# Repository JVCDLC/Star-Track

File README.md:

# ⭐ Star-Track by JVCDLC

## 🚀 Overview

**Star-Track** is an open-source project designed to transform a **manual telescope** into a fully **automated tracking system**.

It enables you to:
- 🔭 Automatically locate stars and planets  
- 🎯 Precisely orient the telescope  
- 🔄 Track celestial objects in real time  
- 🔍 Adjust focus dynamically  

The goal is simple: make astronomical observation **faster, easier, and more accessible**.

---

## 📚 Documentation

All setup instructions, technical details, and recommendations are available in the wiki:

👉 **[Star-Track Wiki](https://github.com/JVCDLC/Star-Track/wiki)**

---

## ⚙️ Features

### 🔧 Calibration
Ensure accurate positioning and alignment of your telescope.

https://github.com/user-attachments/assets/175ef95b-0138-4629-bef2-cc6909bee551

---

### 🌐 Web Interface
Control your telescope from a clean and intuitive interface.

---

### 🌌 Celestial Object Alignment
Automatically detect and select stars and planets.

https://github.com/user-attachments/assets/3bd77a46-6f4f-4f7e-8b46-55b38fbb0885

---

### 📡 Tracking
Keep your target centered with continuous real-time tracking.

https://github.com/user-attachments/assets/9ddb90b2-c935-49f4-bd0f-7d9df8abe6cd

---

---

## 📜 License

This project is licensed under the **GNU General Public License v2.0**.

You are free to:
- use
- modify
- distribute

as long as any derivative work is also distributed under the same license.

See the full license here: [LICENSE](./LICENSE)

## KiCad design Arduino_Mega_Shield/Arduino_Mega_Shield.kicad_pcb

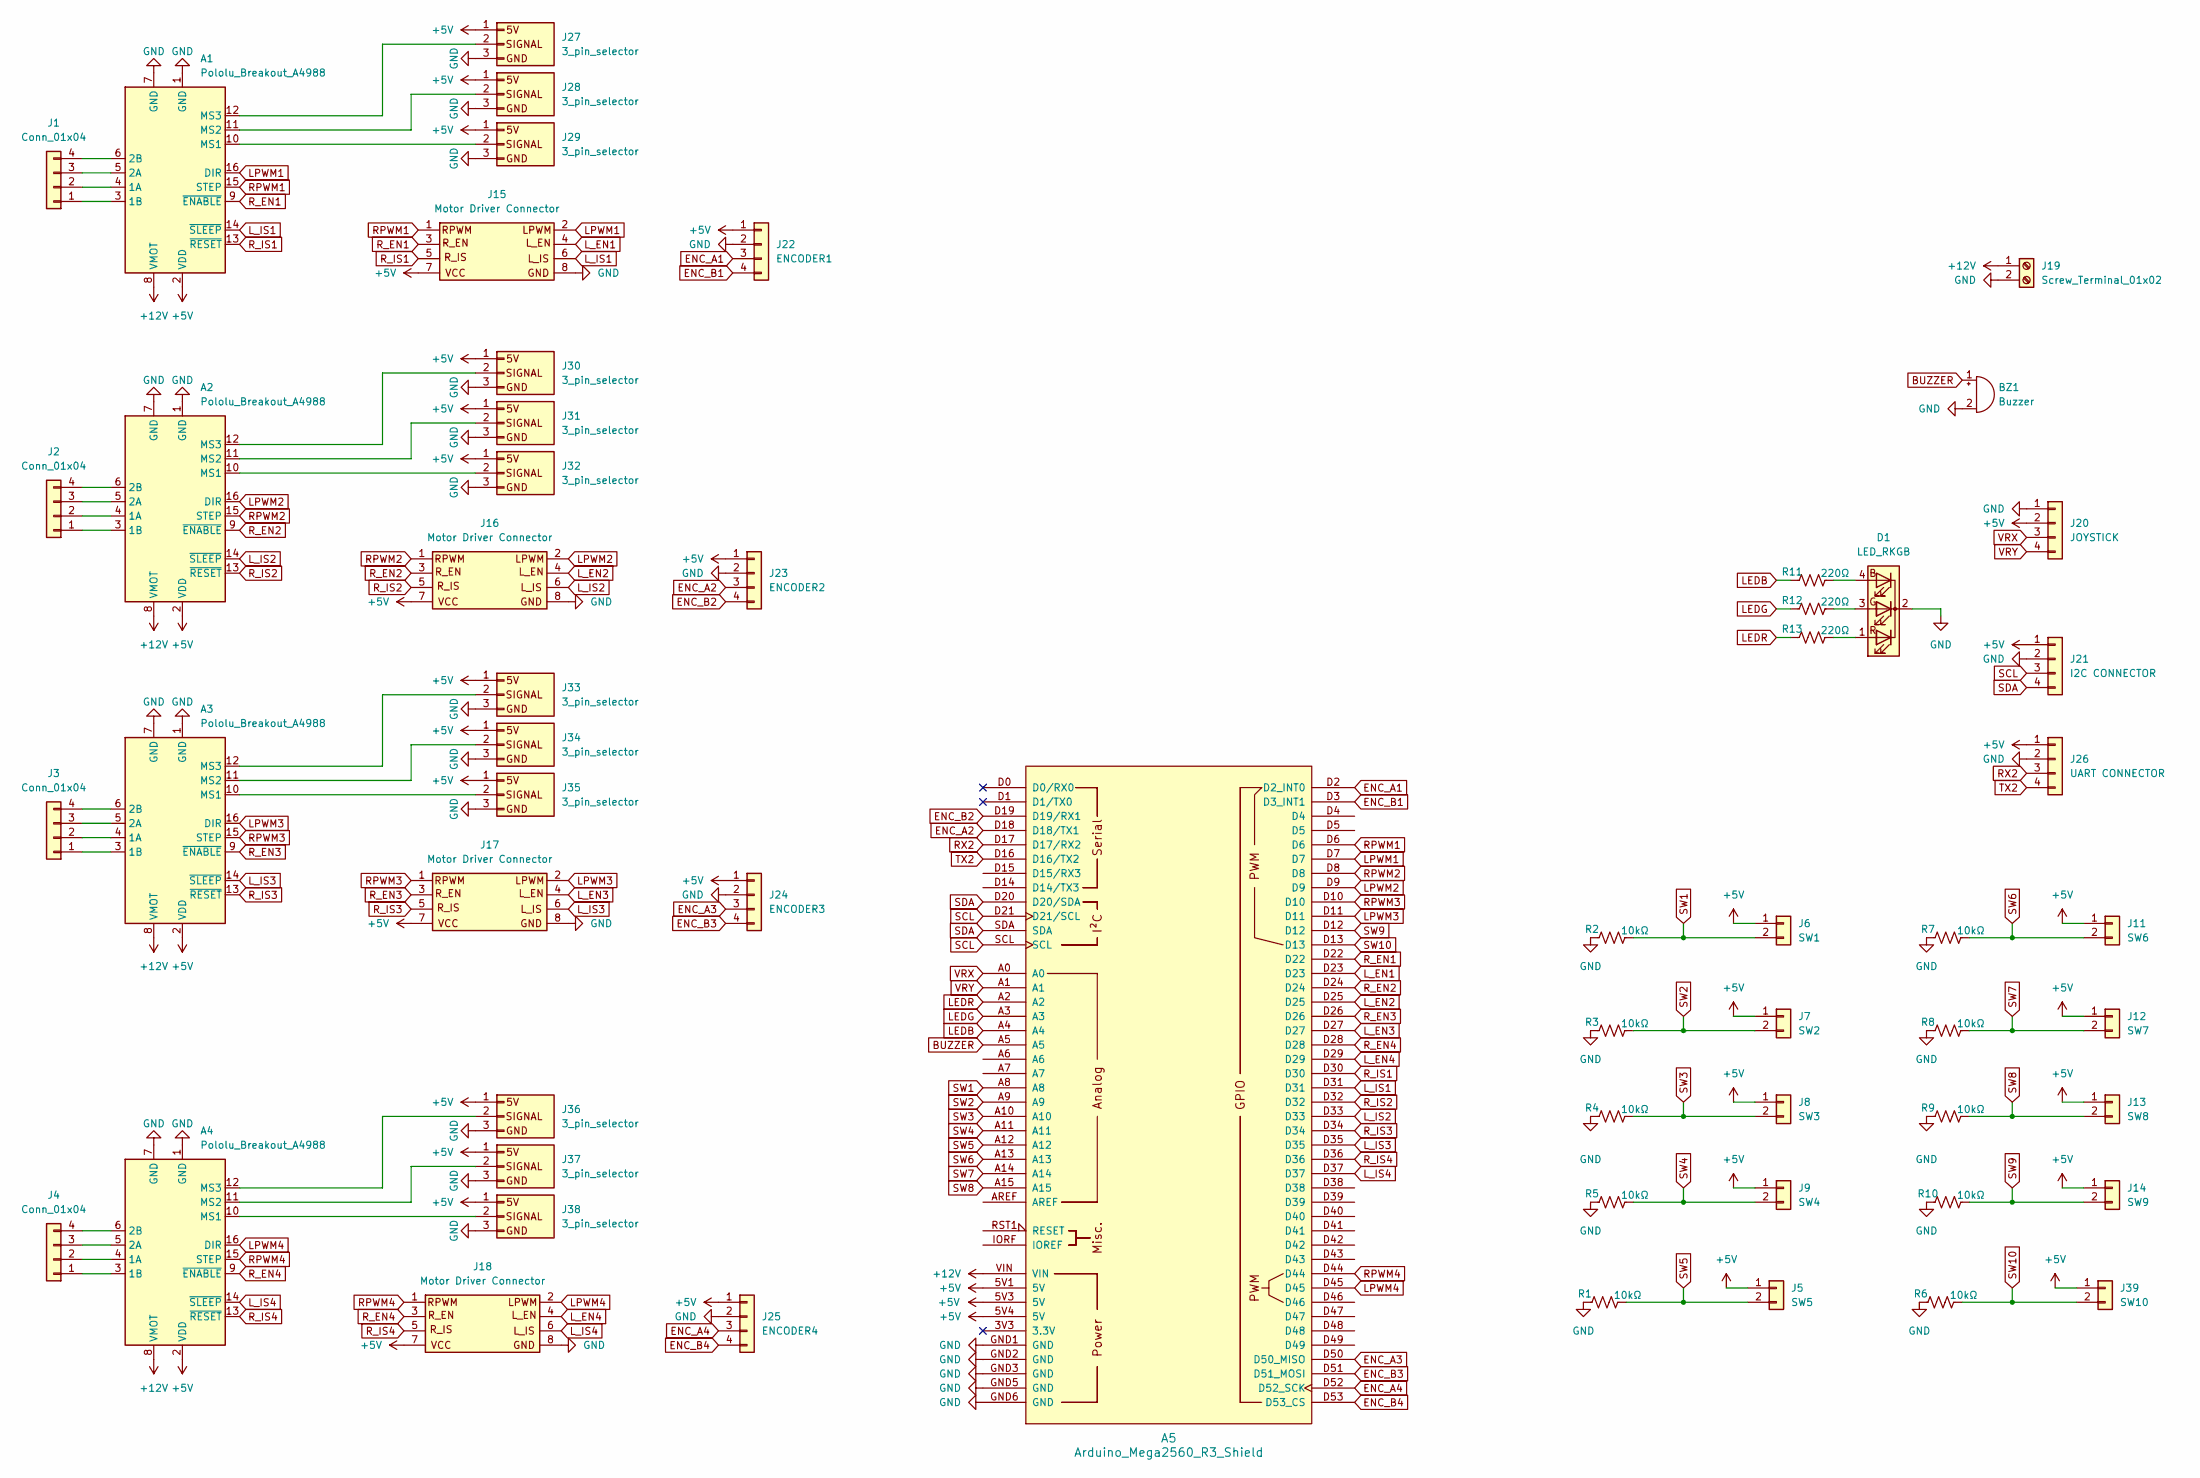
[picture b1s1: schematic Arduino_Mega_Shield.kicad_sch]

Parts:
A1, A2, A3, A4: Pololu_Breakout_A4988; Pololu_Breakout-16_15.2x20.3mm
A5: Arduino_Mega2560_R3_Shield
BZ1: Buzzer; Buzzer_12x9.5RM7.6
D1: LED_RKGB; LED_D5.0mm-4_RGB_Wide_Pins
J1, J2, J3, J4: Conn_01x04; JST_XH_B4B-XH-A_1x04_P2.50mm_Vertical
J5: SW5; PinHeader_1x02_P2.54mm_Vertical
J6: SW1; PinHeader_1x02_P2.54mm_Vertical
J7: SW2; PinHeader_1x02_P2.54mm_Vertical
J8: SW3; PinHeader_1x02_P2.54mm_Vertical
J9: SW4; PinHeader_1x02_P2.54mm_Vertical
J11: SW6; PinHeader_1x02_P2.54mm_Vertical
J12: SW7; PinHeader_1x02_P2.54mm_Vertical
J13: SW8; PinHeader_1x02_P2.54mm_Vertical
J14: SW9; PinHeader_1x02_P2.54mm_Vertical
J15, J16, J17, J18: Motor Driver Connector; PinHeader_2x04_P2.54mm_Vertical
J19: Screw_Terminal_01x02; TerminalBlock_RND_205-00232_1x02_P5.08mm_Horizontal
J20: JOYSTICK; JST_XH_B4B-XH-A_1x04_P2.50mm_Vertical
J21: I2C CONNECTOR; JST_XH_B4B-XH-A_1x04_P2.50mm_Vertical
J22: ENCODER1; JST_XH_B4B-XH-A_1x04_P2.50mm_Vertical
J23: ENCODER2; JST_XH_B4B-XH-A_1x04_P2.50mm_Vertical
J24: ENCODER3; JST_XH_B4B-XH-A_1x04_P2.50mm_Vertical
J25: ENCODER4; JST_XH_B4B-XH-A_1x04_P2.50mm_Vertical
J26: UART CONNECTOR; JST_XH_B4B-XH-A_1x04_P2.50mm_Vertical
J27, J28, J29, J30, J31, J32, J33, J34, J35, J36, J37, J38: 3_pin_selector; 3 pin selector
J39: SW10; PinHeader_1x02_P2.54mm_Vertical
R1, R2, R3, R4, R5, R6, R7, R8, R9, R10: 10kΩ; R_Axial_DIN0207_L6.3mm_D2.5mm_P7.62mm_Horizontal
R11, R12, R13: 220Ω; R_Axial_DIN0207_L6.3mm_D2.5mm_P7.62mm_Horizontal

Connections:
+5V: A1.2 (VDD), A2.2 (VDD), A3.2 (VDD), A4.2 (VDD), A5.5V1 (5V), A5.5V3 (5V), A5.5V4 (5V), J5.1, J6.1, J7.1, J8.1, J9.1, J11.1, J12.1, J13.1, J14.1, J15.7, J16.7, J17.7, J18.7, J20.2, J21.1, J22.1, J23.1, J24.1, J25.1, J26.1, J27.1, J28.1, J29.1, J30.1, J31.1, J32.1, J33.1, J34.1, J35.1, J36.1, J37.1, J38.1, J39.1
+12V: A1.8 (VMOT), A2.8 (VMOT), A3.8 (VMOT), A4.8 (VMOT), A5.VIN, J19.1
BUZZER: A5.A5, BZ1.1 (+)
ENC_A1: A5.D2 (D2_INT0), J22.3
ENC_A2: A5.D18 (D18/TX1), J23.3
ENC_A3: A5.D50 (D50_MISO), J24.3
ENC_A4: A5.D52 (D52_SCK), J25.3
ENC_B1: A5.D3 (D3_INT1), J22.4
ENC_B2: A5.D19 (D19/RX1), J23.4
ENC_B3: A5.D51 (D51_MOSI), J24.4
ENC_B4: A5.D53 (D53_CS), J25.4
GND: A1.1 (GND), A1.7 (GND), A2.1 (GND), A2.7 (GND), A3.1 (GND), A3.7 (GND), A4.1 (GND), A4.7 (GND), A5.GND1 (GND), A5.GND2 (GND), A5.GND3 (GND), A5.GND5 (GND), A5.GND6 (GND), BZ1.2 (-), D1.2 (K), J15.8, J16.8, J17.8, J18.8, J19.2, J20.1, J21.2, J22.2, J23.2, J24.2, J25.2, J26.2, J27.3, J28.3, J29.3, J30.3, J31.3, J32.3, J33.3, J34.3, J35.3, J36.3, J37.3, J38.3, R1.1, R2.1, R3.1, R4.1, R5.1, R6.1, R7.1, R8.1, R9.1, R10.1
LEDB: A5.A4, R11.1
LEDG: A5.A3, R12.1
LEDR: A5.A2, R13.1
LPWM1: A1.16 (DIR), A5.D7, J15.2
LPWM2: A2.16 (DIR), A5.D9, J16.2
LPWM3: A3.16 (DIR), A5.D11, J17.2
LPWM4: A4.16 (DIR), A5.D45, J18.2
L_EN1: A5.D23, J15.4
L_EN2: A5.D25, J16.4
L_EN3: A5.D27, J17.4
L_EN4: A5.D29, J18.4
L_IS1: A1.14 (~SLEEP), A5.D31, J15.6
L_IS2: A2.14 (~SLEEP), A5.D33, J16.6
L_IS3: A3.14 (~SLEEP), A5.D35, J17.6
L_IS4: A4.14 (~SLEEP), A5.D37, J18.6
unnamed: A1.4 (1A), J1.2
unnamed: A1.3 (1B), J1.1
unnamed: A1.5 (2A), J1.3
unnamed: A1.6 (2B), J1.4
unnamed: A1.10 (MS1), J29.2
unnamed: A1.11 (MS2), J28.2
unnamed: A1.12 (MS3), J27.2
unnamed: A2.4 (1A), J2.2
unnamed: A2.3 (1B), J2.1
unnamed: A2.5 (2A), J2.3
unnamed: A2.6 (2B), J2.4
unnamed: A2.10 (MS1), J32.2
unnamed: A2.11 (MS2), J31.2
unnamed: A2.12 (MS3), J30.2
unnamed: A3.4 (1A), J3.2
unnamed: A3.3 (1B), J3.1
unnamed: A3.5 (2A), J3.3
unnamed: A3.6 (2B), J3.4
unnamed: A3.10 (MS1), J35.2
unnamed: A3.11 (MS2), J34.2
unnamed: A3.12 (MS3), J33.2
unnamed: A4.4 (1A), J4.2
unnamed: A4.3 (1B), J4.1
unnamed: A4.5 (2A), J4.3
unnamed: A4.6 (2B), J4.4
unnamed: A4.10 (MS1), J38.2
unnamed: A4.11 (MS2), J37.2
unnamed: A4.12 (MS3), J36.2
unnamed: D1.4 (BA), R11.2
unnamed: D1.3 (GA), R12.2
unnamed: D1.1 (RA), R13.2
RPWM1: A1.15 (STEP), A5.D6, J15.1
RPWM2: A2.15 (STEP), A5.D8, J16.1
RPWM3: A3.15 (STEP), A5.D10, J17.1
RPWM4: A4.15 (STEP), A5.D44, J18.1
RX2: A5.D17 (D17/RX2), J26.3
R_EN1: A1.9 (~ENABLE), A5.D22, J15.3
R_EN2: A2.9 (~ENABLE), A5.D24, J16.3
R_EN3: A3.9 (~ENABLE), A5.D26, J17.3
R_EN4: A4.9 (~ENABLE), A5.D28, J18.3
R_IS1: A1.13 (~RESET), A5.D30, J15.5
R_IS2: A2.13 (~RESET), A5.D32, J16.5
R_IS3: A3.13 (~RESET), A5.D34, J17.5
R_IS4: A4.13 (~RESET), A5.D36, J18.5
SCL: A5.D21 (D21/SCL), A5.SCL, J21.3
SDA: A5.D20 (D20/SDA), A5.SDA, J21.4
SW1: A5.A8, J6.2, R2.2
SW2: A5.A9, J7.2, R3.2
SW3: A5.A10, J8.2, R4.2
SW4: A5.A11, J9.2, R5.2
SW5: A5.A12, J5.2, R1.2
SW6: A5.A13, J11.2, R7.2
SW7: A5.A14, J12.2, R8.2
SW8: A5.A15, J13.2, R9.2
SW9: A5.D12, J14.2, R10.2
SW10: A5.D13, J39.2, R6.2
TX2: A5.D16 (D16/TX2), J26.4
VRX: A5.A0, J20.3
VRY: A5.A1, J20.4

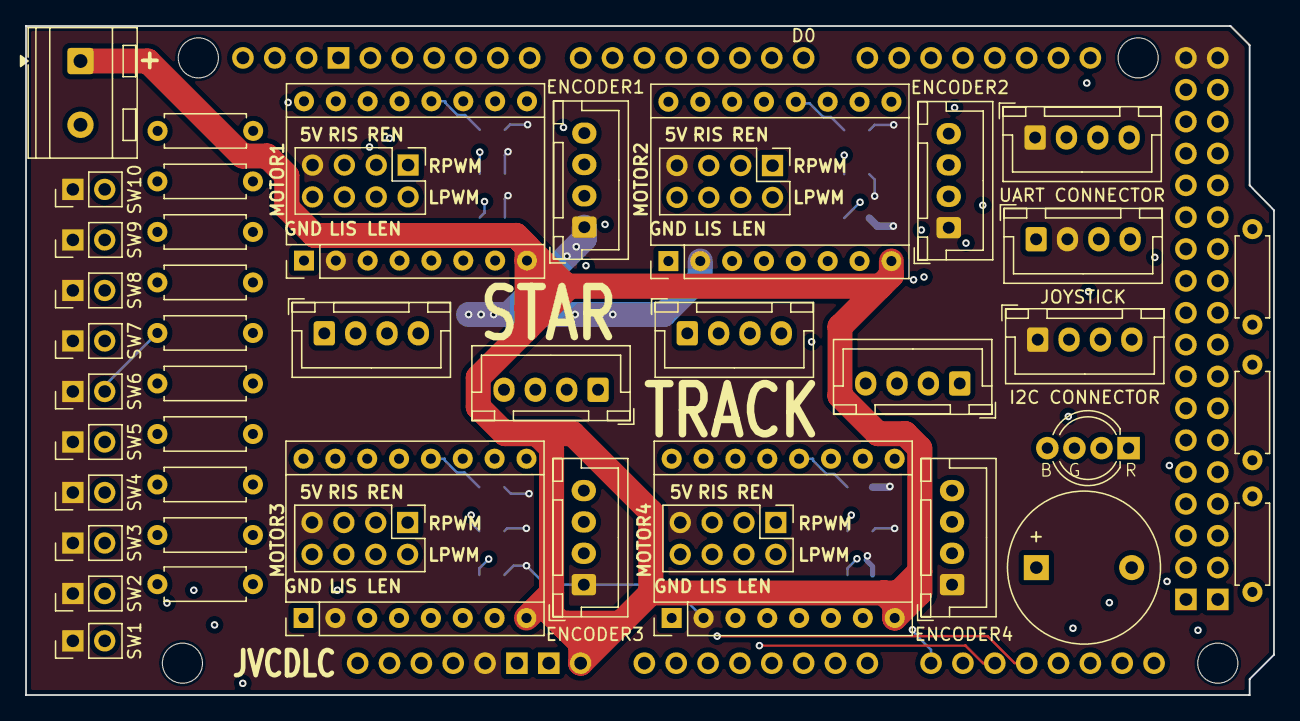
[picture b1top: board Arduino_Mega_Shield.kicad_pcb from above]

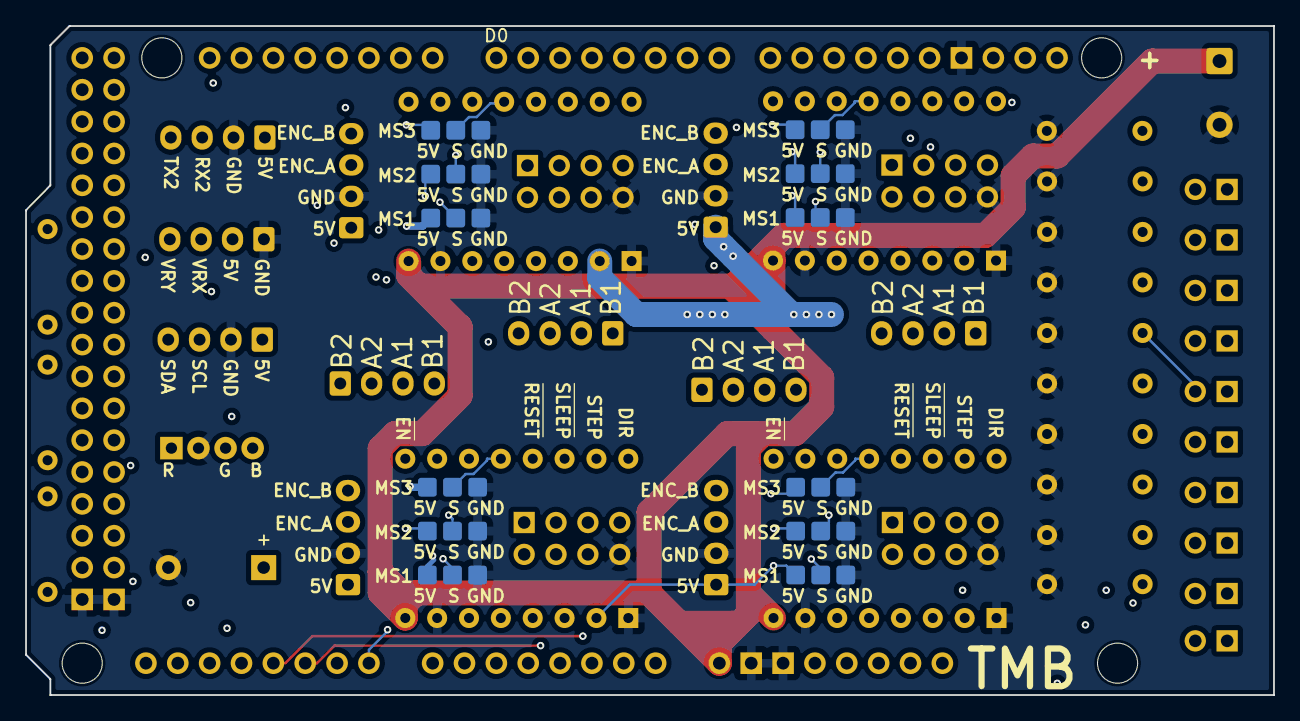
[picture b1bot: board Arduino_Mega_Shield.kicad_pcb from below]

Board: 4 copper layers, 99.5 x 53.3 mm, 58 parts (12 on the bottom side), 86 nets.

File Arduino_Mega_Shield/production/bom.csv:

Designator,Footprint,Quantity,Value,LCSC Part #
"A1, A2, A3, A4",Pololu_Breakout-16_15.2x20.3mm,4,Pololu_Breakout_A4988,
A5,Arduino_Mega2560_R3_Shield,1,Arduino_Mega2560_R3_Shield,
BZ1,Buzzer_12x9.5RM7.6,1,Buzzer,
D1,LED_D5.0mm-4_RGB_Wide_Pins,1,LED_RKGB,
"J1, J2, J3, J4",JST_XH_B4B-XH-A_1x04_P2.50mm_Vertical,4,Conn_01x04,
J11,PinHeader_1x02_P2.54mm_Vertical,1,SW6,
J12,PinHeader_1x02_P2.54mm_Vertical,1,SW7,
J13,PinHeader_1x02_P2.54mm_Vertical,1,SW8,
J14,PinHeader_1x02_P2.54mm_Vertical,1,SW9,
"J15, J16, J17, J18",PinHeader_2x04_P2.54mm_Vertical,4,Motor Driver Connector,
J19,TerminalBlock_RND_205-00232_1x02_P5.08mm_Horizontal,1,Screw_Terminal_01x02,
J20,JST_XH_B4B-XH-A_1x04_P2.50mm_Vertical,1,JOYSTICK,
J21,JST_XH_B4B-XH-A_1x04_P2.50mm_Vertical,1,I2C CONNECTOR,
J22,JST_XH_B4B-XH-A_1x04_P2.50mm_Vertical,1,ENCODER1,
J23,JST_XH_B4B-XH-A_1x04_P2.50mm_Vertical,1,ENCODER2,
J24,JST_XH_B4B-XH-A_1x04_P2.50mm_Vertical,1,ENCODER3,
J25,JST_XH_B4B-XH-A_1x04_P2.50mm_Vertical,1,ENCODER4,
J26,JST_XH_B4B-XH-A_1x04_P2.50mm_Vertical,1,UART CONNECTOR,
"J27, J28, J29, J30, J31, J32, J33, J34, J35, J36, J37, J38",3 pin selector,12,3_pin_selector,
J39,PinHeader_1x02_P2.54mm_Vertical,1,SW10,
J5,PinHeader_1x02_P2.54mm_Vertical,1,SW5,
J6,PinHeader_1x02_P2.54mm_Vertical,1,SW1,
J7,PinHeader_1x02_P2.54mm_Vertical,1,SW2,
J8,PinHeader_1x02_P2.54mm_Vertical,1,SW3,
J9,PinHeader_1x02_P2.54mm_Vertical,1,SW4,
"R1, R10, R2, R3, R4, R5, R6, R7, R8, R9",R_Axial_DIN0207_L6.3mm_D2.5mm_P7.62mm_Horizontal,10,10kΩ,
"R11, R12, R13",R_Axial_DIN0207_L6.3mm_D2.5mm_P7.62mm_Horizontal,3,220Ω,

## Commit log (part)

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2026-01-14 Update README.md
    Added OnShape Link
2026-01-14 Create field_of_view.py and update .gitignore. The python script evaluates the angular size of celestial bodies and compares it with the effective field of view of a telescope. The results are used t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
    Uncomment .idea/ and .vscode/ to make Git ignore those folders.
2026-01-14 Add requirements.txt List Python dependencies required to run the project. To install them, run: "pip install -r requirements.txt".
2026-01-16 Switch from static image to real-time webcam processing
    Replaces static image analysis with real-time video capture from the webcam. Adds live contour detection, center and diameter calculation, and overlays results on the video stream. Exits loop on 'q' 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
2026-01-16 Add References.txt with sky view resource
    Added a References.txt file containing a link to Stellarium Web for sky view by date.
2026-01-27 Add initial ESP-32 embedded and Python communication code
    Added PlatformIO project structure for ESP-32, including .gitignore, configuration, and a basic Arduino sketch that echoes serial messages with an ACK prefix. Also added a Python script to send and r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
2026-01-27 Add motor control request function for ESP-32
    Introduced Motor enum and send_request_motor function to send motor position requests to ESP-32 and handle acknowledgments. Updated main loop to demonstrate motor control requests and improved serial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
2026-01-28 Add motor control and encoder handling for ESP32
    Replaced Mega2560 config with ESP32 in platformio.ini. Implemented encoder reading, BTS7960 motor driver control, and basic PID logic in main.cpp. Enhanced serial command parsing and response. Update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
2026-01-28 Refactor motor control and add constants header
    Moved motor and encoder constants to a new motor_constants.hpp file for better organization and maintainability. Updated main.cpp to use the new constants, refactored variable names for clarity, and 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
2026-01-30 Update motor pin mappings and Python control loop
    Added color-coded comments to motor pin definitions and updated pin assignments for RA motor in motor_constants.hpp. Modified main.py to incrementally update the target angle for the RIGHT_ASCENSION 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
2026-01-30 Typing error correction in field_of_view.py script.
2026-02-03 Add ESP32-C3 MPU6050 accelerometer project
    Add a new PlatformIO project for ESP32-C3 to read an MPU6050 accelerometer. New files: .gitignore, platformio.ini (esp32-c3-devkitm-1, Arduino framework, USB build flags, Adafruit MPU6050/Unified Sen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
2026-02-03 Add RA motor support and PID + calibration
    Extend motor control to support a second (RA) motor and improve PID control and calibration. Key changes:
    - Add RA-specific encoder state, ISR, drive, reading, PID state and update functions.
    - Split DEC drive/encoder functions and refactor update_motor into DEC_update_motor and RA_update_motor; combined update_motor calls both.
    - Add integral (Ki) term with anti-windup for both motors and reset integral on new targets.
    - Replace single minimal-PWM detection with calibrate_minimum_PWM() that tests DEC and RA separately and stores DEC_pwm_min_real and RA_pwm_min_real.
    - Update setup() to initialize RA hardware, attach RA interrupts, and configure PWM
2026-02-03 DEC motor functionning, RA motor not working
    Adjust motor control parameters and improve calibration/debugging:
    - Set initial minimal PWM for both motors to 150.
    - Enable REN/LEN lines in DEC/RA drive functions before writing PWM.
    - Change RA driver PWM pin (RA_RPWM) from 15 to 17.
    - Increase RA PID proportional gain (RA_Kp) from 15.0 to 100.0.
    - Improve minimum-PWM detection: add serial logging, increase sample delay, raise motion threshold, and alter RA search start value.
2026-02-11 Working version!! Keyboard control; refine calibration & pins
    Add interactive keyboard control to Python client and harden motor calibration in firmware.
    Python: import msvcrt and add a non-blocking keyboard loop to send WASD controls and adjust speed with arrow keys (send_request_motor helper added). The previous continuous test loop is commented out.
    Firmware (ESP32): change DEC_LPWM and RA_LPWM pin assignments, add DEC_pwm_start_max and RA_pwm_start_max, and set RA gearbox to 900. Improve minimum PWM detection by printing motor-specific test mes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
2026-02-11 Use discrete speed presets with index
    Replace continuous speed_factor stepping with a discrete list of calibrated speed_values and a speed_index. Initialize speed_factor from speed_values[speed_index] and remove speed_step/min/max. Up/do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
2026-02-15 Update KiCad PCB (Pololu A4988) and ESP32 code
    Replace Arduino Mega shield footprint with a Pololu A4988 breakout footprint and reorganize PCB item positions/annotations (silkscreen, fab, footprint properties, net index adjustments). Add several 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
2026-02-16 Update code to analyse image and rename pictures
2026-02-17 Revise KiCad PCB footprints and add backups
    Large update to the Arduino_Mega_Shield KiCad project: modified .kicad_pcb/.kicad_prl/.kicad_pro/.kicad_sch to replace and update connector footprints (JST XH, pin headers), adjust pad shapes/drills,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
2026-02-18 Avancement on the electric shemas and some fixe on the PCB
2026-02-18 Some mast modification before changing for a Arduino Mega
2026-02-18 rencenter movemanual
2026-02-18 Change the code to work on a Arduino Mega and change the timers to be silent
    Switch project from ESP32 to ATmega2560 (PlatformIO env changed to megaatmega2560). Replace ESP32 ledc PWM APIs with Arduino analogWrite/pinMode and configure timer prescalers (TCCRnB) for quieter PW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
2026-02-23 PCB trace, but not verified
2026-02-24 First revision of the PCB
2026-02-24 Refactor movement control and update vision
    Recenter.py: Large refactor of movement/control logic — renamed and uppercased constants, added Skyfield timescale, introduced MOVEMENTSTATE enum, implemented raTracking, rotateXYtoAltAz, moveManuall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
    astrononic_function.py: Minor cleanup around main() and visible-catalog printing (whitespace/comment adjustments).
    recording_asi.py: Adjusted ASI camera defaults (gain/exposure), switched to RAW16 for deep-sky capture and fixed frame dtype/reshape to
2026-02-24 Add Jupiter video processing script
    Adds Software/Vision/src/video_test.py: a simple OpenCV pipeline that downsamples frames, thresholds and finds largest contour to locate a center, computes focus via Laplacian variance (with a rollin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
2026-03-01 Final version of the PCB
2026-03-07 Refactor of the Arduino code to improve readability and debugging
2026-03-09 Add astronomical operator and recentering functionality; remove unused recenter.py
2026-03-10 Enhance FOCUS motor control and tuning
    Adjust FOCUS control parameters and add safety/behavior changes.
    - constants.hpp: set FOCUS_gearbox to 75.0 and increase FOCUS_Kp to 1.0 to correct gearing and strengthen proportional control.
    - motors.cpp:
    - In FOCUS_drive_motor invert/constrain PWM to match wiring and prevent movement into switch by zeroing PWM when switch1 is triggered.
    - Increase delay in FOCUS_find_minimum_PWM() calibration from 200ms to 400ms.
    - Call FOCUS_update_motor() from update_motor() so focus is updated together with other axes.
2026-03-11 UpdateCatalog w rising and setting
2026-03-11 Update catalog rising and setting
2026-03-11 Add phone communication features with WebSocket and video streaming basically adding the whole UI - Implemented app.js for handling video stream and WebSocket communication. - Added main.py to contro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
2026-03-11 NOT WORKING Detect RA angle range; reduce start PWM
    Lowered PWM start maxima (DEC/RA/FOCUS) from 150 to 120 to reduce calibration drive power. Implemented RA angle-range detection: added RA_find_angle_range(), global min/max angle variables, and proto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
2026-03-14 - Developed a complete multi-pass autofocus state machine (sweep, analyze, lock, and track) with previous code from JP. - Implemented a highly realistic `ArduinoController` simulator featuring dual-P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
2026-03-20 Try to debug the code
    Add an exported interactive BOM (ibom.html) for the Arduino_Mega_Shield, including the embedded CSS/JS viewer (Split.js, LZString, pointer-event polyfills, etc.). Also apply updates to the ESP-32 emb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
2026-03-21 Calibration of declimation is working with switch
2026-03-22 The RA calibration is almost working
    Refine motor calibration routines for RA/DEC and add focus calibration. Changes include: calling RA_find_angle_range() from setup; removing unused static vars; tightening encoder centering threshold 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
2026-03-25 Finally have a working version of the calibration.
2026-03-27 Refactor motor control and serial protocol for improved clarity and functionality
    - Enhanced MotorState and MotionMode enums with detailed comments for better understanding of each state.
    - Updated PidConfig, MotorRuntimeConfig, LimitConfig, CalibrationConfig, and PrecisionConfig structures with descriptive comments for clarity on their purpose and usage.
    - Improved MotorBase class documentation, outlining its responsibilities and design principles.
    - Refined MountController class with comprehensive comments explaining its architecture, usage, and member functions.
    - Added detailed comments in SerialProtocol class to clarify the parsing logic and command structure.
    - Introduced a new DEBUG_F
2026-03-27 degree to ticks in astronomic operator
2026-03-28 improve readability of electrical shematic
2026-03-28 Revise draw.io schematic: layout & components
    Update Electric shematic.drawio: reorganize component geometry and edges, reposition Raspberry Pi and Camera, rename/expand the Arduino block to "Arduino Mega Shield", specify BTS7960 motor drivers (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
2026-03-29 Add 3D STL parts for gearboxes and mounts
    Add numerous STL assets for 3D printing, organized under DECLIMATION GEARBOX, RIGHT ASCENSION GEARBOX GEARBOX, and OTHER. Includes cycloidal disks, eccentric shafts, rotors/stators, motor mounts, top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
2026-03-29 First commit for integration with working calibration
    Introduce a refactored build env and runtime improvements for motor control: add STARTRACK_ENABLE_REFACTORED_ARCH PlatformIO env and main_refactored build filters. Enhance MD13S motor with filtered s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
2026-03-30 time fix i think
2026-04-01 Add PowerSchema For estimating battery life
2026-04-01 Add and reorganize 3D print STL files
    Add multiple new STL assets (focus parts, tripod bracket parts, electrical skeleton components, and a HOLDER) and include STAR-TRACK (ALL PARTS).zip. Reorganize existing STL files into numbered subfo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
2026-04-01 Rename 3D print files to include quantities
    Batch-rename STL files across '007 - GEARBOX JOINT', '014 - CYCLOIDAL GEARBOX', and '015 - ELECTRICAL SKELETON' to include quantity indicators (e.g. '(2X)', '(4X)', '(6X)'). The renames are identical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
2026-04-01 feat: Initialize camera angle and add functions for coordinate transformation
2026-04-02 Fixing joystick not working when no target.
2026-04-02 Fix joystick speed mapping and DEC scaling
    Swap the speed arguments passed to x_y_to_ha_dec so joystick X/Y map to the intended DEC/RA speeds in both manual-input code paths, and adjust manual_speed_max_dec_deg_s to manual_speed_max_ra_deg_s 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
2026-04-02 Adjust joystick speed calculations and sidereal rate for improved movement control
2026-04-08 Add detailed comments to MotorLink and AstronomicOperator methods for improved code clarity
2026-04-09 Clean Up and Refactor of file system
2026-04-15 Enhance README with project image and details
    Added project image and updated project description.
2026-04-15 Replace Picture2 image link in README.md
2026-04-15 Fix formatting in README.md
2026-04-15 Add new image to README
    Updated the README to include a new image.
2026-04-15 Resize image in README.md
    Updated image size in README and adjusted alignment.
2026-04-16 changement of electric shematic
2026-04-16 Try to add video to the README
2026-04-16 Update README.md
    Add calibration and orientation videos.
2026-04-16 Add images to README for better visualization
    Added images to enhance the README documentation.
2026-04-16 Modify video tags for autoplay and loop functionality
    Updated video elements in README to autoplay, loop, and mute.
2026-04-16 Remove 'Aiming towards the sun' from README
    Removed the phrase 'Aiming towards the sun' from the README.
2026-04-17 Rename section from Detection to Alignment
